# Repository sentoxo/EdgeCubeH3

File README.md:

# EdgeCubeH3
Work in proggress

Custom, cheap, simple and hand-solder single-board computer with allwinner H3 CPU. Compatibilie with Orange Pi One OS's likes Armbian.

## Features

- H3 Quad-Core ARM Cortex-A7 @ 1.2GHz CPU
    - Mali400 MP2 OpenGL ES 2.0 GPU
- 512MiB of DDR3L RAM, 16b
- 16MB SPI FLASH (Optional)
- Ethernet PHY, 100Mb/s
- GPDI video out
- USB connectors:
    - 2x USB-A 
    - 1x USB-C
- uSD card slot
- GPIO
- Small format 52x52mm

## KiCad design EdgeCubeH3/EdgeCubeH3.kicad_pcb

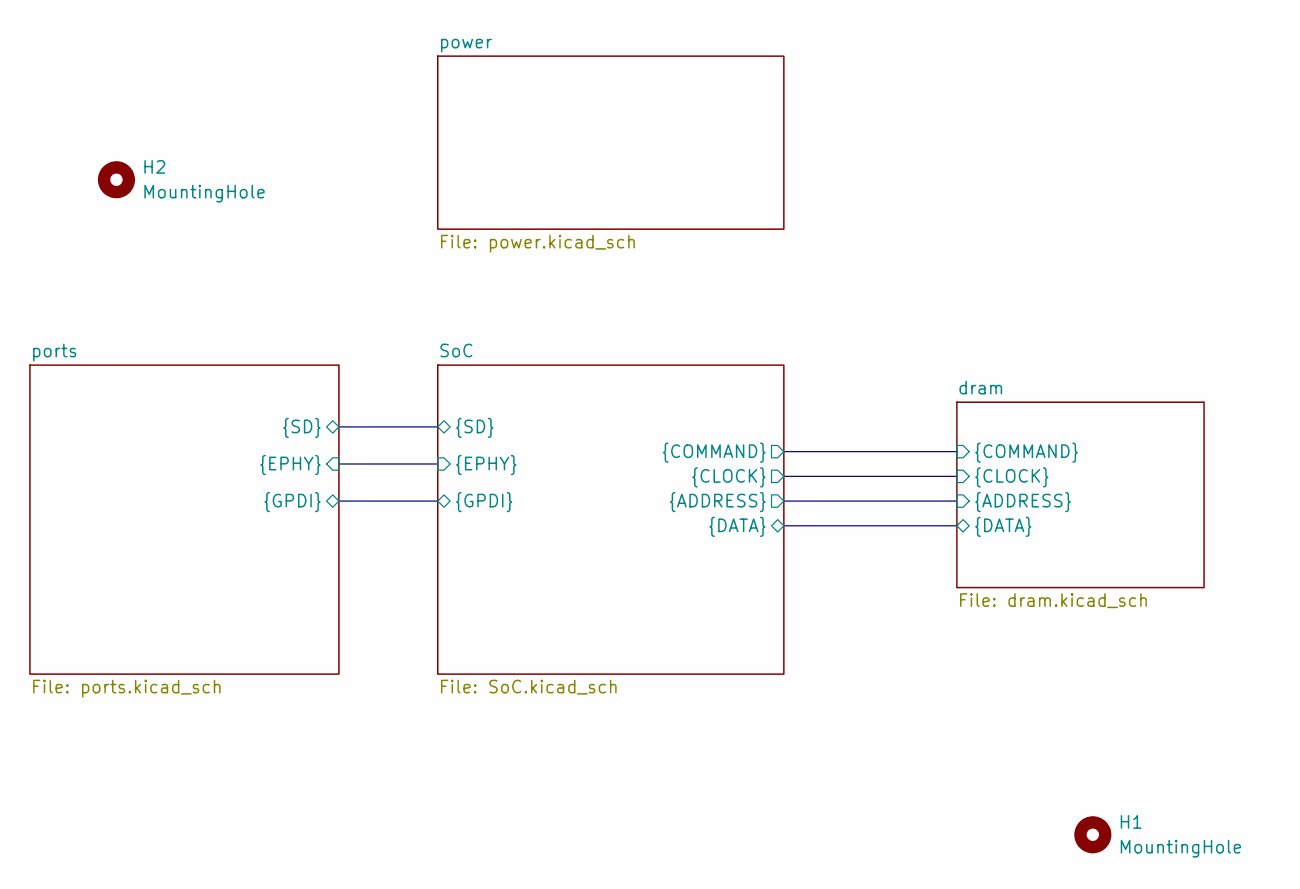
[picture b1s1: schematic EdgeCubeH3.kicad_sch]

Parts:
H1, H2: MountingHole; MountingHole_2.2mm_M2

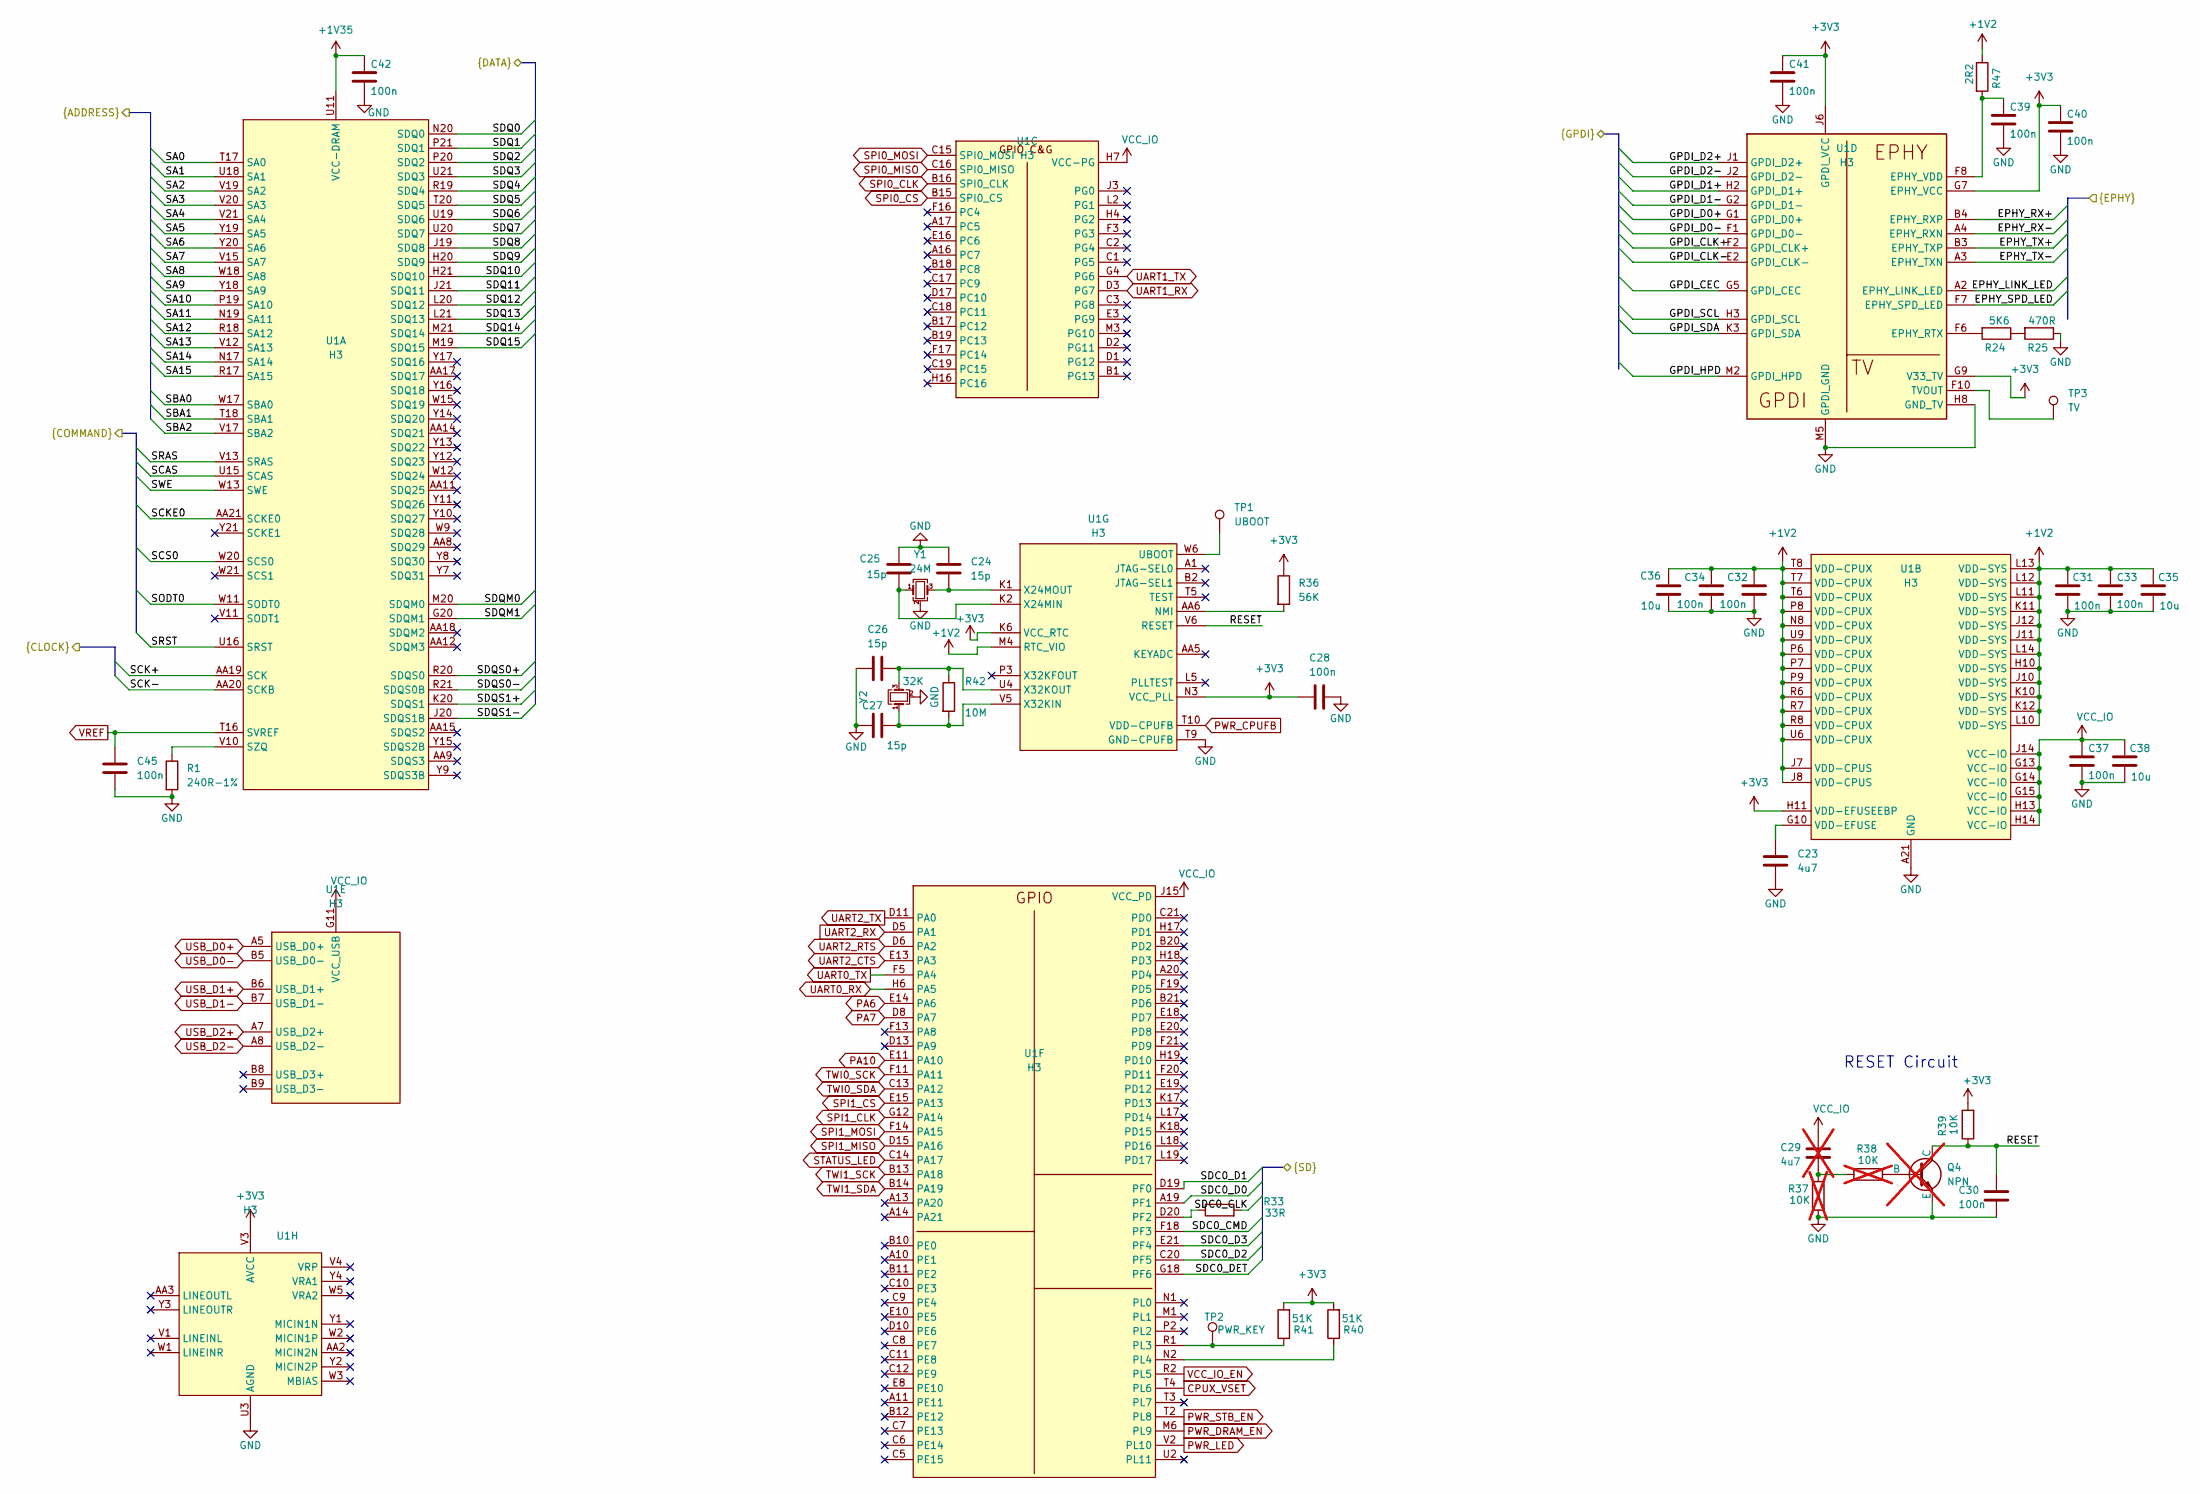
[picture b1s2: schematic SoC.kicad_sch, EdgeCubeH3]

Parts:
C23: 4u7; C_0603_1608Metric
C24, C25, C26, C27: 15p; C_0603_1608Metric
C28, C31, C32, C33, C34, C37, C39, C40, C41, C42: 100n; C_0402_1005Metric
C29: 4u7; C_0603_1608Metric; not fitted
C30: 100n; C_0603_1608Metric
C35, C36, C38: 10u; C_0603_1608Metric
C45: 100n; R_0402_1005Metric
Q4: NPN; TSOT-23; not fitted
R1: 240R-1%; R_0603_1608Metric_Pad0.98x0.95mm_HandSolder
R24: 5K6; R_0603_1608Metric_Pad0.98x0.95mm_HandSolder
R25: 470R; R_0603_1608Metric_Pad0.98x0.95mm_HandSolder
R33: 33R; R_0603_1608Metric_Pad0.98x0.95mm_HandSolder
R36: 56K; R_0603_1608Metric
R37, R38: 10K; R_0603_1608Metric_Pad0.98x0.95mm_HandSolder; not fitted
R39: 10K; R_0603_1608Metric_Pad0.98x0.95mm_HandSolder
R40, R41: 51K; R_0603_1608Metric_Pad0.98x0.95mm_HandSolder
R42: 10M; R_0603_1608Metric
R47: 2R2; R_0603_1608Metric
TP1: UBOOT; TestPoint_Pad_D1.0mm
TP2: PWR_KEY; TestPoint_Pad_D1.0mm
TP3: TV; TestPoint_Pad_D1.0mm
U1: H3; FBGA-347_14x14mm_Layout21x21_P0.65mm
Y1: 24M; Crystal_SMD_3225-4Pin_3.2x2.5mm
Y2: 32K; Crystal_SMD_3225-4Pin_3.2x2.5mm

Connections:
+1V2: C31.1, C32.1, C33.1, C34.1, C35.1, C36.2, R47.1, U1.H10 (VDD-SYS), U1.J7 (VDD-CPUS), U1.J8 (VDD-CPUS), U1.J10 (VDD-SYS), U1.J11 (VDD-SYS), U1.J12 (VDD-SYS), U1.K10 (VDD-SYS), U1.K11 (VDD-SYS), U1.K12 (VDD-SYS), U1.L10 (VDD-SYS), U1.L11 (VDD-SYS), U1.L12 (VDD-SYS), U1.L13 (VDD-SYS), U1.L14 (VDD-SYS), U1.M4 (RTC_VIO), U1.N8 (VDD-CPUX), U1.P6 (VDD-CPUX), U1.P7 (VDD-CPUX), U1.P8 (VDD-CPUX), U1.P9 (VDD-CPUX), U1.R6 (VDD-CPUX), U1.R7 (VDD-CPUX), U1.R8 (VDD-CPUX), U1.T6 (VDD-CPUX), U1.T7 (VDD-CPUX), U1.T8 (VDD-CPUX), U1.U6 (VDD-CPUX), U1.U9 (VDD-CPUX); also elsewhere on the board
+1V35: C42.1, U1.L16 (VCC-DRAM), U1.M16 (VCC-DRAM), U1.N16 (VCC-DRAM), U1.P16 (VCC-DRAM), U1.P17 (VCC-DRAM), U1.R16 (VCC-DRAM), U1.T12 (VCC-DRAM), U1.T13 (VCC-DRAM), U1.T14 (VCC-DRAM), U1.T15 (VCC-DRAM), U1.U11 (VCC-DRAM); also elsewhere on the board
+3V3: C28.1, C40.1, C41.1, R36.1, R39.2, R40.2, R41.2, U1.G7 (EPHY_VCC), U1.G9 (V33_TV), U1.H11 (VDD-EFUSEEBP), U1.J6 (GPDI_VCC), U1.K6 (VCC_RTC), U1.N3 (VCC_PLL), U1.V3 (AVCC); also elsewhere on the board
/SoC/EPHY_LINK_LED: U1.A2 (EPHY_LINK_LED); also elsewhere on the board
/SoC/EPHY_RX+: U1.B4 (EPHY_RXP); also elsewhere on the board
/SoC/EPHY_RX-: U1.A4 (EPHY_RXN); also elsewhere on the board
/SoC/EPHY_SPD_LED: U1.F7 (EPHY_SPD_LED); also elsewhere on the board
/SoC/EPHY_TX+: U1.B3 (EPHY_TXP); also elsewhere on the board
/SoC/EPHY_TX-: U1.A3 (EPHY_TXN); also elsewhere on the board
/SoC/GPDI_CEC: U1.G5 (GPDI_CEC); also elsewhere on the board
/SoC/GPDI_CLK+: U1.F2 (GPDI_CLK+); also elsewhere on the board
/SoC/GPDI_CLK-: U1.E2 (GPDI_CLK-); also elsewhere on the board
/SoC/GPDI_D0+: U1.G1 (GPDI_D0+); also elsewhere on the board
/SoC/GPDI_D0-: U1.F1 (GPDI_D0-); also elsewhere on the board
/SoC/GPDI_D1+: U1.H2 (GPDI_D1+); also elsewhere on the board
/SoC/GPDI_D1-: U1.G2 (GPDI_D1-); also elsewhere on the board
/SoC/GPDI_D2+: U1.J1 (GPDI_D2+); also elsewhere on the board
/SoC/GPDI_D2-: U1.J2 (GPDI_D2-); also elsewhere on the board
/SoC/GPDI_HPD: U1.M2 (GPDI_HPD); also elsewhere on the board
/SoC/GPDI_SCL: U1.H3 (GPDI_SCL); also elsewhere on the board
/SoC/GPDI_SDA: U1.K3 (GPDI_SDA); also elsewhere on the board
/SoC/RESET: C30.1, Q4.1 (C), R39.1, U1.V6 (RESET)
/SoC/SA0: U1.T17 (SA0); also elsewhere on the board
/SoC/SA1: U1.U18 (SA1); also elsewhere on the board
/SoC/SA2: U1.V19 (SA2); also elsewhere on the board
/SoC/SA3: U1.V20 (SA3); also elsewhere on the board
/SoC/SA4: U1.V21 (SA4); also elsewhere on the board
/SoC/SA5: U1.Y19 (SA5); also elsewhere on the board
/SoC/SA6: U1.Y20 (SA6); also elsewhere on the board
/SoC/SA7: U1.V15 (SA7); also elsewhere on the board
/SoC/SA8: U1.W18 (SA8); also elsewhere on the board
/SoC/SA9: U1.Y18 (SA9); also elsewhere on the board
/SoC/SA10: U1.P19 (SA10); also elsewhere on the board
/SoC/SA11: U1.N19 (SA11); also elsewhere on the board
/SoC/SA12: U1.R18 (SA12); also elsewhere on the board
/SoC/SA13: U1.V12 (SA13); also elsewhere on the board
/SoC/SA14: U1.N17 (SA14); also elsewhere on the board
/SoC/SA15: U1.R17 (SA15); also elsewhere on the board
/SoC/SBA0: U1.W17 (SBA0); also elsewhere on the board
/SoC/SBA1: U1.T18 (SBA1); also elsewhere on the board
/SoC/SBA2: U1.V17 (SBA2); also elsewhere on the board
/SoC/SCAS: U1.U15 (SCAS); also elsewhere on the board
/SoC/SCK+: U1.AA19 (SCK); also elsewhere on the board
/SoC/SCK-: U1.AA20 (SCKB); also elsewhere on the board
/SoC/SCKE0: U1.AA21 (SCKE0); also elsewhere on the board
/SoC/SCS0: U1.W20 (SCS0); also elsewhere on the board
/SoC/SDC0_CLK: R33.2; also elsewhere on the board
/SoC/SDC0_CMD: U1.F18 (PF3); also elsewhere on the board
/SoC/SDC0_D0: U1.A19 (PF1); also elsewhere on the board
/SoC/SDC0_D1: U1.D19 (PF0); also elsewhere on the board
/SoC/SDC0_D2: U1.C20 (PF5); also elsewhere on the board
/SoC/SDC0_D3: U1.E21 (PF4); also elsewhere on the board
/SoC/SDC0_DET: U1.G18 (PF6); also elsewhere on the board
/SoC/SDQ0: U1.N20 (SDQ0); also elsewhere on the board
/SoC/SDQ1: U1.P21 (SDQ1); also elsewhere on the board
/SoC/SDQ2: U1.P20 (SDQ2); also elsewhere on the board
/SoC/SDQ3: U1.U21 (SDQ3); also elsewhere on the board
/SoC/SDQ4: U1.R19 (SDQ4); also elsewhere on the board
/SoC/SDQ5: U1.T20 (SDQ5); also elsewhere on the board
/SoC/SDQ6: U1.U19 (SDQ6); also elsewhere on the board
/SoC/SDQ7: U1.U20 (SDQ7); also elsewhere on the board
/SoC/SDQ8: U1.J19 (SDQ8); also elsewhere on the board
/SoC/SDQ9: U1.H20 (SDQ9); also elsewhere on the board
/SoC/SDQ10: U1.H21 (SDQ10); also elsewhere on the board
/SoC/SDQ11: U1.J21 (SDQ11); also elsewhere on the board
/SoC/SDQ12: U1.L20 (SDQ12); also elsewhere on the board
/SoC/SDQ13: U1.L21 (SDQ13); also elsewhere on the board
/SoC/SDQ14: U1.M21 (SDQ14); also elsewhere on the board
/SoC/SDQ15: U1.M19 (SDQ15); also elsewhere on the board
/SoC/SDQM0: U1.M20 (SDQM0); also elsewhere on the board
/SoC/SDQM1: U1.G20 (SDQM1); also elsewhere on the board
/SoC/SDQS0+: U1.R20 (SDQS0); also elsewhere on the board
/SoC/SDQS0-: U1.R21 (SDQS0B); also elsewhere on the board
/SoC/SDQS1+: U1.K20 (SDQS1); also elsewhere on the board
/SoC/SDQS1-: U1.J20 (SDQS1B); also elsewhere on the board
/SoC/SODT0: U1.W11 (SODT0); also elsewhere on the board
/SoC/SRAS: U1.V13 (SRAS); also elsewhere on the board
/SoC/SRST: U1.U16 (SRST); also elsewhere on the board
/SoC/SWE: U1.W13 (SWE); also elsewhere on the board
CPUX_VSET: U1.T4 (PL6); also elsewhere on the board
GND: C23.2, C24.1, C25.2, C26.1, C27.1, C28.2, C30.2, C31.2, C32.2, C33.2, C34.2, C35.2, C36.1, C37.2, C38.2, C39.2, C40.2, C41.2, C42.2, C45.2, Q4.3 (E), R1.2, R25.1, R37.2, U1.A21 (GND), U1.AA1 (GND), U1.G8 (GND), U1.H8 (GND_TV), U1.H12 (GND), U1.H15 (GND), U1.J9 (GND), U1.J13 (GND), U1.J16 (GND), U1.K7 (GND), U1.K8 (GND), U1.K9 (GND), U1.K13 (GND), U1.K14 (GND), U1.K15 (GND), U1.K16 (GND), U1.L8 (GND), U1.L9 (GND), U1.L15 (GND), U1.M5 (GPDI_GND), U1.M7 (GND), U1.M8 (GND), U1.M9 (GND), U1.M10 (GND), U1.M11 (GND), U1.M12 (GND), U1.M13 (GND), U1.M14 (GND), U1.M15 (GND), U1.N7 (GND), U1.N9 (GND), U1.N10 (GND), U1.N11 (GND), U1.N12 (GND), U1.N13 (GND), U1.N14 (GND), U1.N15 (GND), U1.P10 (GND), U1.P11 (GND), U1.P12 (GND), U1.P13 (GND), U1.P14 (GND), U1.P15 (GND), U1.R9 (GND), U1.R10 (GND), U1.R11 (GND), U1.R12 (GND), U1.R13 (GND), U1.R14 (GND), U1.T9 (GND-CPUFB), U1.T11 (GND), U1.U3 (AGND), Y1.2 (G), Y1.4 (G), Y2.2 (G), Y2.4 (G); also elsewhere on the board
unnamed: C29.2, R37.1, R38.1
unnamed: Q4.2 (B), R38.2
unnamed: R24.1, R25.2
unnamed: R1.1, U1.V10 (SZQ)
unnamed: C23.1, U1.G10 (VDD-EFUSE)
unnamed: R24.2, U1.F6 (EPHY_RTX)
unnamed: C39.1, R47.2, U1.F8 (EPHY_VDD)
unnamed: TP3.1 (1_1), U1.F10 (TVOUT)
unnamed: R33.1, U1.D20 (PF2)
unnamed: R41.1, TP2.1 (1_1), U1.R1 (PL3)
unnamed: R40.1, U1.N2 (PL4)
unnamed: R36.2, U1.AA6 (NMI)
unnamed: TP1.1 (1_1), U1.W6 (UBOOT)
unnamed: C25.1, U1.K2 (X24MIN), Y1.1
unnamed: C24.2, U1.K1 (X24MOUT), Y1.3
unnamed: C27.2, R42.2, U1.V5 (X32KIN), Y2.1
unnamed: C26.2, R42.1, U1.U4 (X32KOUT), Y2.3
PA6: U1.E14 (PA6); also elsewhere on the board
PA7: U1.D8 (PA7); also elsewhere on the board
PA10: U1.E11 (PA10); also elsewhere on the board
PWR_CPUFB: U1.T10 (VDD-CPUFB); also elsewhere on the board
PWR_DRAM_EN: U1.M6 (PL9); also elsewhere on the board
PWR_LED: U1.V2 (PL10); also elsewhere on the board
PWR_STB_EN: U1.T2 (PL8); also elsewhere on the board
SPI0_CLK: U1.B16 (SPI0_CLK); also elsewhere on the board
SPI0_CS: U1.B15 (SPI0_CS); also elsewhere on the board
SPI0_MISO: U1.C16 (SPI0_MISO); also elsewhere on the board
SPI0_MOSI: U1.C15 (SPI0_MOSI); also elsewhere on the board
SPI1_CLK: U1.G12 (PA14); also elsewhere on the board
SPI1_CS: U1.E15 (PA13); also elsewhere on the board
SPI1_MISO: U1.D15 (PA16); also elsewhere on the board
SPI1_MOSI: U1.F14 (PA15); also elsewhere on the board
STATUS_LED: U1.C14 (PA17); also elsewhere on the board
TWI0_SCK: U1.F11 (PA11); also elsewhere on the board
TWI0_SDA: U1.C13 (PA12); also elsewhere on the board
TWI1_SCK: U1.B13 (PA18); also elsewhere on the board
TWI1_SDA: U1.B14 (PA19); also elsewhere on the board
UART0_RX: U1.H6 (PA5); also elsewhere on the board
UART0_TX: U1.F5 (PA4); also elsewhere on the board
UART1_RX: U1.D3 (PG7); also elsewhere on the board
UART1_TX: U1.G4 (PG6); also elsewhere on the board
UART2_CTS: U1.E13 (PA3); also elsewhere on the board
UART2_RTS: U1.D6 (PA2); also elsewhere on the board
UART2_RX: U1.D5 (PA1); also elsewhere on the board
UART2_TX: U1.D11 (PA0); also elsewhere on the board
USB_D0+: U1.A5 (USB_D0+); also elsewhere on the board
USB_D0-: U1.B5 (USB_D0-); also elsewhere on the board
USB_D1+: U1.B6 (USB_D1+); also elsewhere on the board
USB_D1-: U1.B7 (USB_D1-); also elsewhere on the board
USB_D2+: U1.A7 (USB_D2+); also elsewhere on the board
USB_D2-: U1.A8 (USB_D2-); also elsewhere on the board
VCC_IO: C29.1, C37.1, C38.1, U1.G11 (VCC_USB), U1.G13 (VCC-IO), U1.G14 (VCC-IO), U1.G15 (VCC-IO), U1.H7 (VCC-PG), U1.H13 (VCC-IO), U1.H14 (VCC-IO), U1.J14 (VCC-IO), U1.J15 (VCC_PD); also elsewhere on the board
VCC_IO_EN: U1.R2 (PL5); also elsewhere on the board
VREF: C45.1, U1.T16 (SVREF); also elsewhere on the board

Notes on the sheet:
RESET Circuit

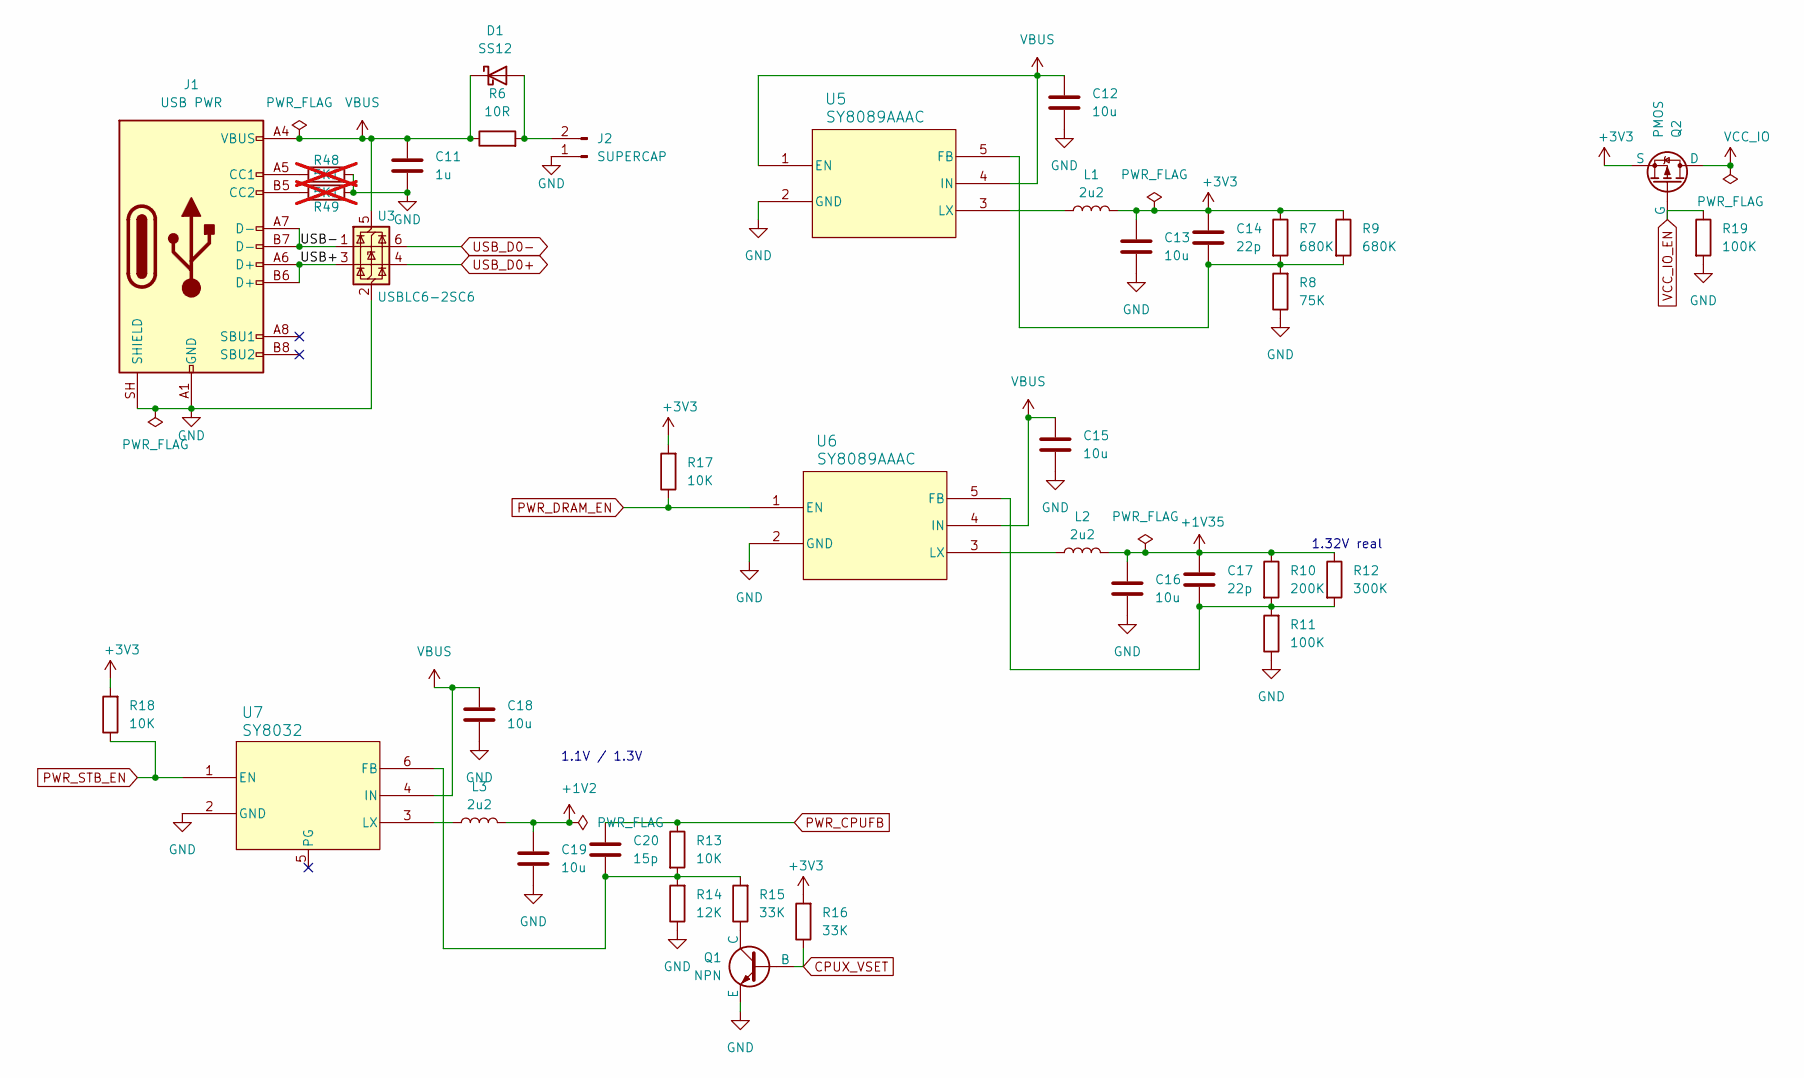
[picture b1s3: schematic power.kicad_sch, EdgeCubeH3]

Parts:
C11: 1u; C_0603_1608Metric
C12, C13, C15, C16, C18, C19: 10u; C_0603_1608Metric
C14, C17: 22p; C_0603_1608Metric
C20: 15p; C_0603_1608Metric
D1: SS12; D_SMA
J1: USB PWR; USB_C_Receptacle_HRO_TYPE-C-31-M-12
J2: SUPERCAP; PinHeader_1x02_P1.27mm_Vertical
L1, L2, L3: 2u2; L_APV_APH0420
Q1: NPN; TSOT-23
Q2: PMOS; SOT-23W
R6: 10R; R_1206_3216Metric
R7, R9: 680K; C_0603_1608Metric
R8: 75K; C_0603_1608Metric
R10: 200K; C_0603_1608Metric
R11: 100K; C_0603_1608Metric
R12: 300K; C_0603_1608Metric
R13, R17, R18: 10K; R_0603_1608Metric
R14: 12K; R_0603_1608Metric
R15, R16: 33K; R_0603_1608Metric
R19: 100K; R_0603_1608Metric_Pad0.98x0.95mm_HandSolder
R48, R49: 5K1; R_0603_1608Metric; not fitted
U3: USBLC6-2SC6; SOT-23-6
U5, U6: SY8089AAAC; SY8089AAAC_SGY
U7: SY8032; SOT-23-6

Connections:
+1V2: C19.1, L3.2; also elsewhere on the board
+1V35: C16.1, C17.1, L2.2, R10.1, R12.1; also elsewhere on the board
+3V3: C13.1, C14.1, L1.2, Q2.3 (S), R7.1, R9.1, R16.2, R17.2, R18.2; also elsewhere on the board
/power/USB+: J1.A6 (D+), J1.B6 (D+), U3.3 (I/O2)
/power/USB-: J1.A7 (D-), J1.B7 (D-), U3.1 (I/O1)
CPUX_VSET: Q1.2 (B), R16.1; also elsewhere on the board
GND: C11.2, C12.2, C13.2, C15.2, C16.2, C18.2, C19.2, J1.A1 (GND), J1.A12 (GND), J1.B1 (GND), J1.B12 (GND), J1.SH (SHIELD), J2.1, Q1.3 (E), R8.1, R11.1, R14.1, R19.2, R48.2, R49.1, U3.2 (GND), U5.2 (GND), U6.2 (GND), U7.2 (GND); also elsewhere on the board
unnamed: D1.2 (A), J2.2, R6.2
unnamed: J1.A5 (CC1), R48.1
unnamed: J1.B5 (CC2), R49.2
unnamed: Q1.1 (C), R15.1
unnamed: C14.2, R7.2, R8.2, R9.2, U5.5 (FB)
unnamed: L1.1, U5.3 (LX)
unnamed: C17.2, R10.2, R11.2, R12.2, U6.5 (FB)
unnamed: L2.1, U6.3 (LX)
unnamed: C20.2, R13.2, R14.2, R15.2, U7.6 (FB)
unnamed: L3.1, U7.3 (LX)
PWR_CPUFB: C20.1, R13.1; also elsewhere on the board
PWR_DRAM_EN: R17.1, U6.1 (EN); also elsewhere on the board
PWR_STB_EN: R18.1, U7.1 (EN); also elsewhere on the board
USB_D0+: U3.4 (I/O2); also elsewhere on the board
USB_D0-: U3.6 (I/O1); also elsewhere on the board
VBUS: C11.1, C12.1, C15.1, C18.1, D1.1 (K), J1.A4 (VBUS), J1.A9 (VBUS), J1.B4 (VBUS), J1.B9 (VBUS), R6.1, U3.5 (VBUS), U5.1 (EN), U5.4 (IN), U6.4 (IN), U7.4 (IN); also elsewhere on the board
VCC_IO: Q2.1 (D); also elsewhere on the board
VCC_IO_EN: Q2.2 (G), R19.1; also elsewhere on the board

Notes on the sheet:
1.32V real
1.1V / 1.3V

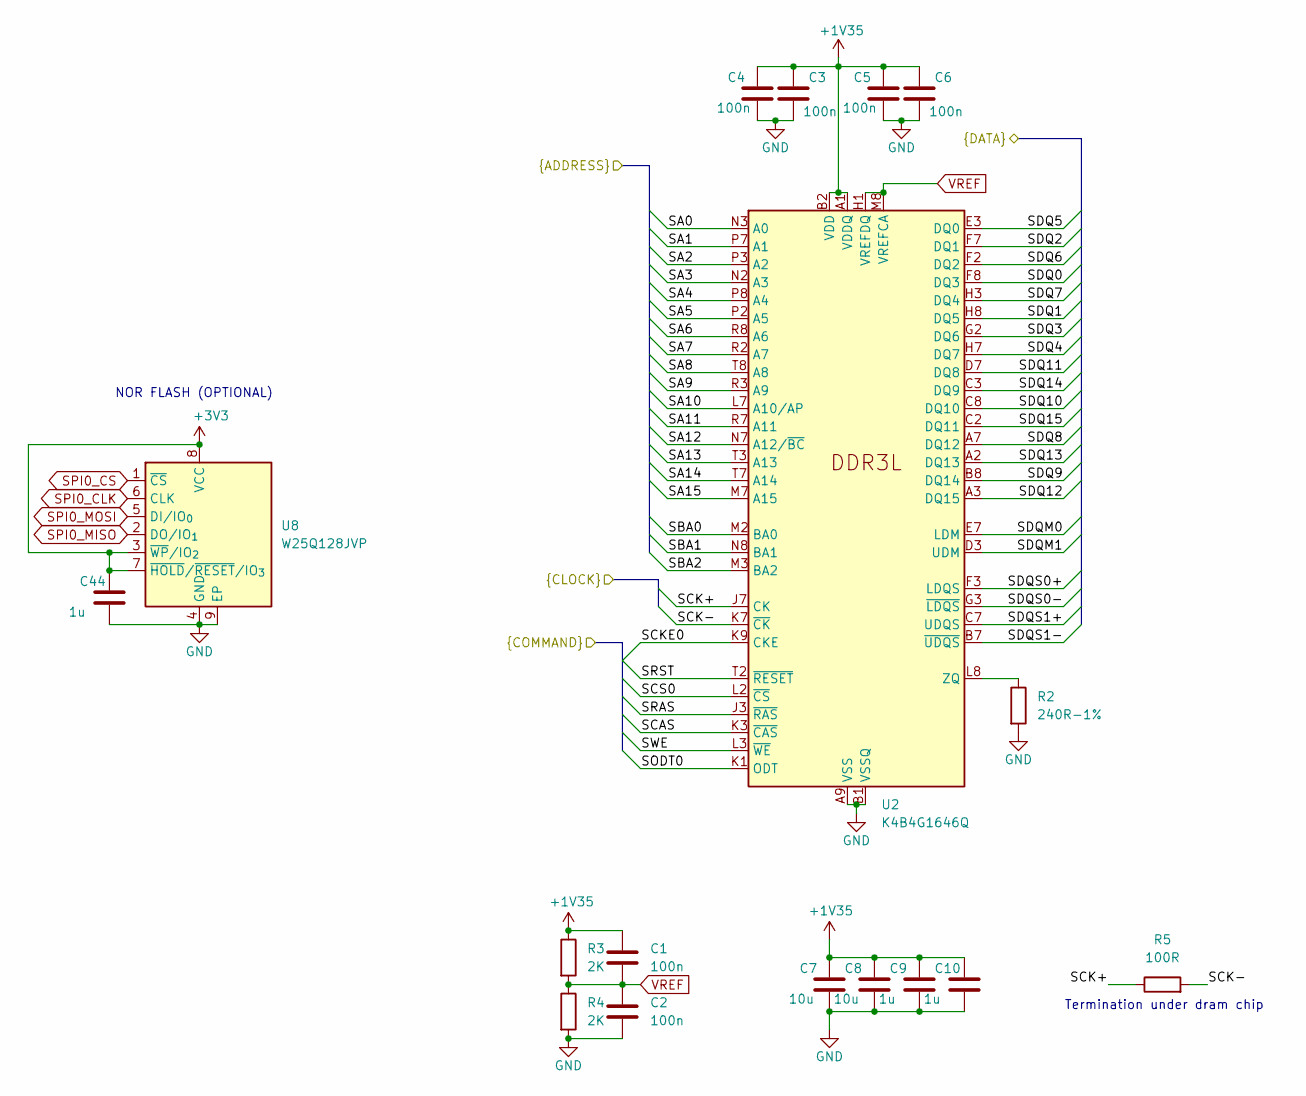
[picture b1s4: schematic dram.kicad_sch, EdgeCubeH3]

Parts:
C1, C2: 100n; C_0603_1608Metric
C3, C4, C5, C6: 100n; C_0402_1005Metric
C7, C8: 10u; C_0603_1608Metric
C9, C10, C44: 1u; C_0603_1608Metric
R2: 240R-1%; R_0603_1608Metric_Pad0.98x0.95mm_HandSolder
R3, R4: 2K; R_0603_1608Metric
R5: 100R; R_0402_1005Metric
U2: K4B4G1646Q; FBGA-96_7.5x13mm_Layout9x16_P0.8mm
U8: W25Q128JVP; WSON-8-1EP_6x5mm_P1.27mm_EP3.4x4.3mm

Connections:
+1V35: C1.1, C3.1, C4.1, C5.1, C6.1, C7.1, C8.1, C9.1, C10.1, R3.1, U2.A1 (VDDQ), U2.A8 (VDDQ), U2.B2 (VDD), U2.C1 (VDDQ), U2.C9 (VDDQ), U2.D2 (VDDQ), U2.D9 (VDD), U2.E9 (VDDQ), U2.F1 (VDDQ), U2.G7 (VDD), U2.H2 (VDDQ), U2.H9 (VDDQ), U2.K2 (VDD), U2.K8 (VDD), U2.N1 (VDD), U2.N9 (VDD), U2.R1 (VDD), U2.R9 (VDD); also elsewhere on the board
+3V3: C44.1, U8.3 (~WP/IO_{2}), U8.7 (~HOLD/~RESET/IO_{3}), U8.8 (VCC); also elsewhere on the board
/SoC/SA0: U2.N3 (A0); also elsewhere on the board
/SoC/SA1: U2.P7 (A1); also elsewhere on the board
/SoC/SA2: U2.P3 (A2); also elsewhere on the board
/SoC/SA3: U2.N2 (A3); also elsewhere on the board
/SoC/SA4: U2.P8 (A4); also elsewhere on the board
/SoC/SA5: U2.P2 (A5); also elsewhere on the board
/SoC/SA6: U2.R8 (A6); also elsewhere on the board
/SoC/SA7: U2.R2 (A7); also elsewhere on the board
/SoC/SA8: U2.T8 (A8); also elsewhere on the board
/SoC/SA9: U2.R3 (A9); also elsewhere on the board
/SoC/SA10: U2.L7 (A10/AP); also elsewhere on the board
/SoC/SA11: U2.R7 (A11); also elsewhere on the board
/SoC/SA12: U2.N7 (A12/~BC); also elsewhere on the board
/SoC/SA13: U2.T3 (A13); also elsewhere on the board
/SoC/SA14: U2.T7 (A14); also elsewhere on the board
/SoC/SA15: U2.M7 (A15); also elsewhere on the board
/SoC/SBA0: U2.M2 (BA0); also elsewhere on the board
/SoC/SBA1: U2.N8 (BA1); also elsewhere on the board
/SoC/SBA2: U2.M3 (BA2); also elsewhere on the board
/SoC/SCAS: U2.K3 (~CAS); also elsewhere on the board
/SoC/SCK+: R5.1, U2.J7 (CK); also elsewhere on the board
/SoC/SCK-: R5.2, U2.K7 (~CK); also elsewhere on the board
/SoC/SCKE0: U2.K9 (CKE); also elsewhere on the board
/SoC/SCS0: U2.L2 (~CS); also elsewhere on the board
/SoC/SDQ0: U2.F8 (DQ3); also elsewhere on the board
/SoC/SDQ1: U2.H8 (DQ5); also elsewhere on the board
/SoC/SDQ2: U2.F7 (DQ1); also elsewhere on the board
/SoC/SDQ3: U2.G2 (DQ6); also elsewhere on the board
/SoC/SDQ4: U2.H7 (DQ7); also elsewhere on the board
/SoC/SDQ5: U2.E3 (DQ0); also elsewhere on the board
/SoC/SDQ6: U2.F2 (DQ2); also elsewhere on the board
/SoC/SDQ7: U2.H3 (DQ4); also elsewhere on the board
/SoC/SDQ8: U2.A7 (DQ12); also elsewhere on the board
/SoC/SDQ9: U2.B8 (DQ14); also elsewhere on the board
/SoC/SDQ10: U2.C8 (DQ10); also elsewhere on the board
/SoC/SDQ11: U2.D7 (DQ8); also elsewhere on the board
/SoC/SDQ12: U2.A3 (DQ15); also elsewhere on the board
/SoC/SDQ13: U2.A2 (DQ13); also elsewhere on the board
/SoC/SDQ14: U2.C3 (DQ9); also elsewhere on the board
/SoC/SDQ15: U2.C2 (DQ11); also elsewhere on the board
/SoC/SDQM0: U2.E7 (LDM); also elsewhere on the board
/SoC/SDQM1: U2.D3 (UDM); also elsewhere on the board
/SoC/SDQS0+: U2.F3 (LDQS); also elsewhere on the board
/SoC/SDQS0-: U2.G3 (~LDQS); also elsewhere on the board
/SoC/SDQS1+: U2.C7 (UDQS); also elsewhere on the board
/SoC/SDQS1-: U2.B7 (~UDQS); also elsewhere on the board
/SoC/SODT0: U2.K1 (ODT); also elsewhere on the board
/SoC/SRAS: U2.J3 (~RAS); also elsewhere on the board
/SoC/SRST: U2.T2 (~RESET); also elsewhere on the board
/SoC/SWE: U2.L3 (~WE); also elsewhere on the board
GND: C2.2, C3.2, C4.2, C5.2, C6.2, C7.2, C8.2, C9.2, C10.2, C44.2, R2.2, R4.2, U2.A9 (VSS), U2.B1 (VSSQ), U2.B3 (VSS), U2.B9 (VSSQ), U2.D1 (VSSQ), U2.D8 (VSSQ), U2.E1 (VSS), U2.E2 (VSSQ), U2.E8 (VSSQ), U2.F9 (VSSQ), U2.G1 (VSSQ), U2.G8 (VSS), U2.G9 (VSSQ), U2.J2 (VSS), U2.J8 (VSS), U2.M1 (VSS), U2.M9 (VSS), U2.P1 (VSS), U2.P9 (VSS), U2.T1 (VSS), U2.T9 (VSS), U8.4 (GND), U8.9 (EP); also elsewhere on the board
unnamed: R2.1, U2.L8 (ZQ)
SPI0_CLK: U8.6 (CLK); also elsewhere on the board
SPI0_CS: U8.1 (~CS); also elsewhere on the board
SPI0_MISO: U8.2 (DO/IO_{1}); also elsewhere on the board
SPI0_MOSI: U8.5 (DI/IO_{0}); also elsewhere on the board
VREF: C1.2, C2.1, R3.2, R4.1, U2.H1 (VREFDQ), U2.M8 (VREFCA); also elsewhere on the board

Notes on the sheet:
Termination under dram chip
NOR FLASH (OPTIONAL)
